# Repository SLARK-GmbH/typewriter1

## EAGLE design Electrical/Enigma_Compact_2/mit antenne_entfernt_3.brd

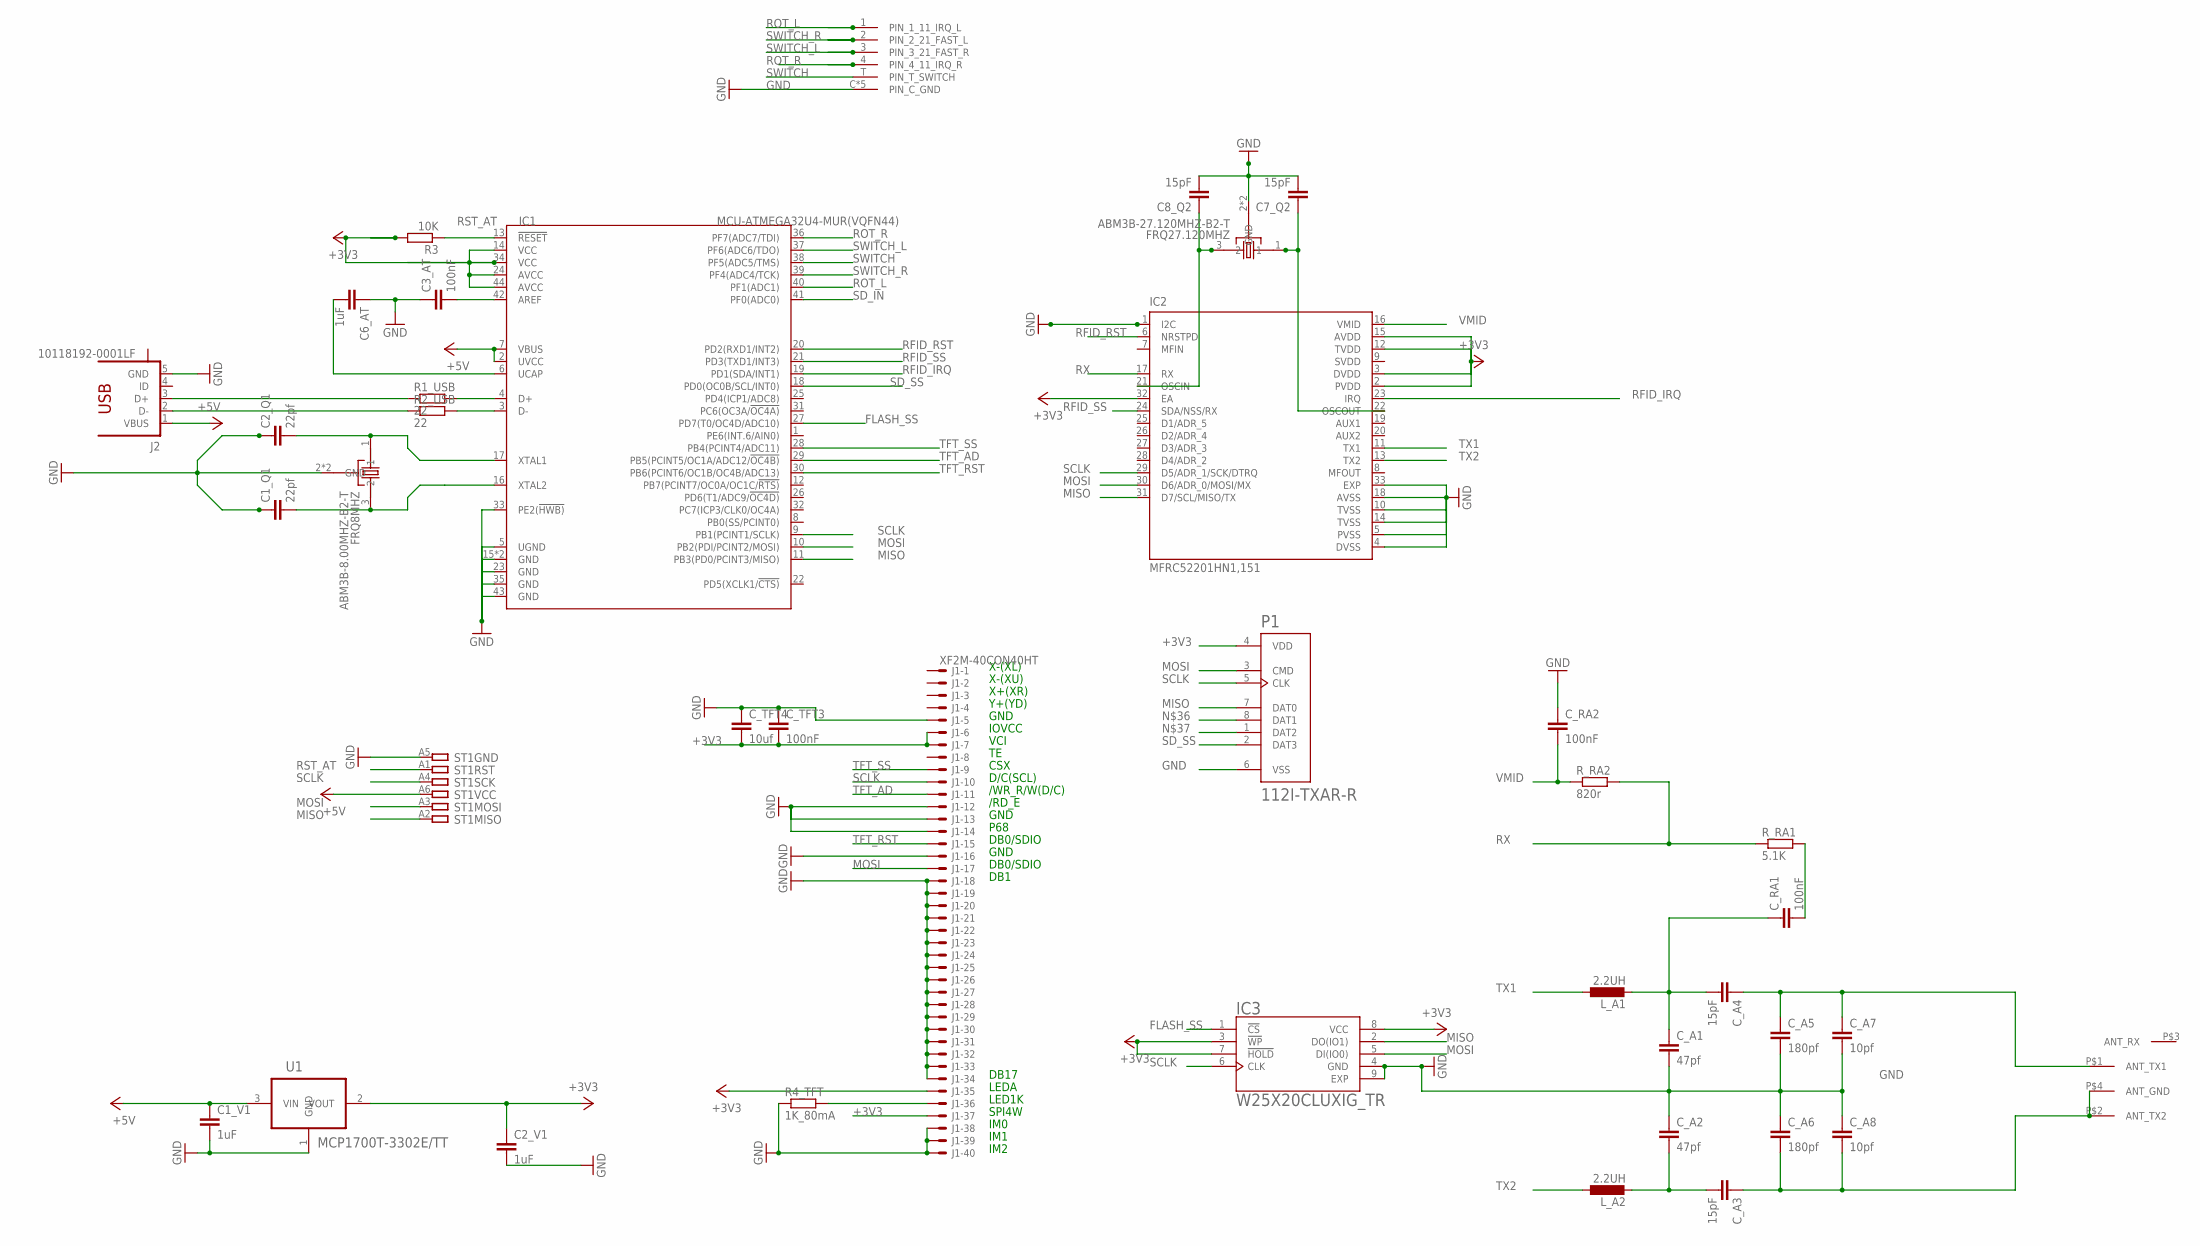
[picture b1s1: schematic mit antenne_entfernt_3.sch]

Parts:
C1_Q1, C2_Q1: 22pf; C0402K
C1_V1, C2_V1, C6_AT: 1uF; C0402K
C3_AT: 100nF; C0402K
C7_Q2, C8_Q2: 15pF; C0402K
C_A1, C_A2: 47pf; C0402K
C_A3: 15pF; C0402K
C_A4: 15pF; C0603K
C_A5, C_A6: 180pf; C0402K
C_A7, C_A8: 10pf; C0402K
C_RA1, C_RA2: 100nF; C0402K
C_TFT3: 100nF; C0402K
C_TFT4: 10uf; C0402K
FRQ8MHZ: ABM3B-8.00MHZ-B2-T; OSCSC500X320X110-4N
FRQ27.120MHZ: ABM3B-27.120MHZ-B2-T; OSCSC500X320X110-4N
IC1: MCU-ATMEGA32U4-MUR(VQFN44); QFN44G-0.5-7X7MM
IC2: MFRC52201HN1,151; QFN50P500X500X100-33N
IC3: W25X20CLUXIG_TR; SON50P300X200X60-9N
J1: XF2M-40CON40HT; XF2M-4015-1F
J2: 10118192-0001LF
L_A1, L_A2: 2.2UH; L2012C
P1: 112I-TXAR-R
R1_USB, R2_USB: 22; R0402
R3: 10K; R0402
R4_TFT: 1K_80mA; R0402
R_RA1: 5.1K; R0402
R_RA2: 820r; R0402
S1: WIPPSCHALTER_SCHWARZ_5WEGE; SMD_SWITCH1
S3: ANTENNE; ANTENNE_ENIGMA_34X44
ST1: ISA; IBM8BIT
U1: MCP1700T-3302E/TT; SOT95P237X112-3N

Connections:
+3V3: C2_V1.1, C_TFT3.2, C_TFT4.2, IC1.14 (VCC), IC1.24 (AVCC), IC1.34 (VCC), IC1.44 (AVCC), IC2.2 (PVDD), IC2.3 (DVDD), IC2.12 (TVDD), IC2.15 (AVDD), IC2.32 (EA), IC3.3 (!WP), IC3.7 (!HOLD), IC3.8 (VCC), J1.4 (MS), J1.6 (MS), J1.34 (MS), J1.35 (MS), P1.4 (VDD), R3.2, U1.2 (VOUT)
+5V: C1_V1.1, IC1.2 (UVCC), IC1.7 (VBUS), J2.1 (VBUS), ST1.A6, U1.3 (VIN)
FLASH_SS: IC1.27 (PD7(T0/OC4D/ADC10)), IC3.1 (!CS)
GND: C1_Q1.1, C1_V1.2, C2_Q1.1, C2_V1.2, C3_AT.1, C6_AT.1, C7_Q2.2, C8_Q2.2, C_A1.2, C_A2.1, C_A5.2, C_A6.1, C_A7.2, C_A8.1, C_RA2.1, C_TFT3.1, C_TFT4.1, FRQ8MHZ.2 (GND), FRQ8MHZ.4 (GND), FRQ27.120MHZ.2 (GND), FRQ27.120MHZ.4 (GND), IC1.5 (UGND), IC1.15 (GND), IC1.23 (GND), IC1.33 (PE2(!HWB)), IC1.35 (GND), IC1.43 (GND), IC1.TAB (GND), IC2.1 (I2C), IC2.4 (DVSS), IC2.5 (PVSS), IC2.10 (TVSS), IC2.14 (TVSS), IC2.18 (AVSS), IC2.33 (EXP), IC3.4 (GND), IC3.9 (EXP), J1.1 (MS), J1.2 (MS), J1.3 (MS), J1.7 (MS), J1.8 (MS), J1.9 (MS), J1.10 (MS), J1.11 (MS), J1.12 (MS), J1.13 (MS), J1.14 (MS), J1.15 (MS), J1.16 (MS), J1.17 (MS), J1.18 (MS), J1.19 (MS), J1.20 (MS), J1.21 (MS), J1.22 (MS), J1.23 (MS), J1.25 (MS), J1.27 (MS), J1.28 (MS), J1.29 (MS), J1.36 (MS), J1.M1 (MS), J1.M2 (MS), J2.5 (GND), P1.6 (VSS), R4_TFT.1, S1.C (PIN_C_GND), S1.C_1 (PIN_C_GND), S1.C_2 (PIN_C_GND), S1.C_3 (PIN_C_GND), S1.GND_TERMINAL (PIN_C_GND), ST1.A5, U1.1 (GND)
MISO: IC1.11 (PB3(PD0/PCINT3/MISO)), IC2.31 (D7/SCL/MISO/TX), IC3.2 (DO(IO1)), P1.7 (DAT0), ST1.A2
MOSI: IC1.10 (PB2(PDI/PCINT2/MOSI)), IC2.30 (D6/ADR_0/MOSI/MX), IC3.5 (DI(IO0)), J1.24 (MS), P1.3 (CMD), ST1.A3
unnamed: C1_Q1.2, FRQ8MHZ.3 (2), IC1.16 (XTAL2)
unnamed: C2_Q1.2, FRQ8MHZ.1, IC1.17 (XTAL1)
unnamed: C8_Q2.1, FRQ27.120MHZ.3 (2), IC2.21 (OSCIN)
unnamed: IC1.4 (D+), R1_USB.2
unnamed: IC1.3 (D-), R2_USB.2
unnamed: J2.3 (D+), R1_USB.1
unnamed: J2.2 (D-), R2_USB.1
unnamed: C7_Q2.1, FRQ27.120MHZ.1, IC2.22 (OSCOUT)
unnamed: C_A3.1, C_A6.2, C_A8.2, S3.P$2 (ANT_TX2), S3.P$4 (ANT_GND)
unnamed: C3_AT.2, IC1.42 (AREF)
unnamed: C6_AT.2, IC1.6 (UCAP)
unnamed: J1.5 (MS), R4_TFT.2
unnamed: C_RA1.2, R_RA1.2
unnamed: C_A2.2, C_A3.2, L_A2.2
unnamed: C_A1.1, C_A4.2, C_RA1.1, L_A1.2
unnamed: C_A4.1, C_A5.1, C_A7.1, S3.P$1 (ANT_TX1)
RFID_IRQ: IC1.19 (PD1(SDA/INT1)), IC2.23 (IRQ)
RFID_RST: IC1.20 (PD2(RXD1/INT2)), IC2.6 (NRSTPD)
RFID_SS: IC1.21 (PD3(TXD1/INT3)), IC2.24 (SDA/NSS/RX)
ROT_L: IC1.40 (PF1(ADC1)), S1.1 (PIN_1_11_IRQ_L)
ROT_R: IC1.36 (PF7(ADC7/TDI)), S1.4 (PIN_4_11_IRQ_R)
RST_AT: IC1.13 (!RESET), R3.1, ST1.A1
RX: IC2.17 (RX), R_RA1.1, R_RA2.2
SCLK: IC1.9 (PB1(PCINT1/SCLK)), IC2.29 (D5/ADR_1/SCK/DTRQ), IC3.6 (CLK), J1.31 (MS), P1.5 (CLK), ST1.A4
SD_IN: IC1.41 (PF0(ADC0))
SD_SS: IC1.18 (PD0(OC0B/SCL/INT0)), P1.2 (DAT3)
SVDD: IC2.9 (SVDD)
SWITCH: IC1.38 (PF5(ADC5/TMS)), S1.T (PIN_T_SWITCH)
SWITCH_L: IC1.37 (PF6(ADC6/TDO)), S1.3 (PIN_3_21_FAST_R)
SWITCH_R: IC1.39 (PF4(ADC4/TCK)), S1.2 (PIN_2_21_FAST_L)
TFT_AD: IC1.29 (PB5(PCINT5/OC1A/ADC12/!OC4B)), J1.30 (MS)
TFT_RST: IC1.30 (PB6(PCINT6/OC1B/OC4B/ADC13)), J1.26 (MS)
TFT_SS: IC1.28 (PB4(PCINT4/ADC11)), J1.32 (MS)
TX1: IC2.11 (TX1), L_A1.1
TX2: IC2.13 (TX2), L_A2.1
VMID: C_RA2.2, IC2.16 (VMID), R_RA2.1

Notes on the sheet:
X-(XL)
X-(XU)
X+(XR)
Y+(YD)
GND
IOVCC
VCI
CSX
D/C(SCL)
/WR_R/W(D/C)
/RD_E
P68
DB0/SDIO
DB1
DB17
LEDA
LED1K
SPI4W
IM1
IM0
IM2

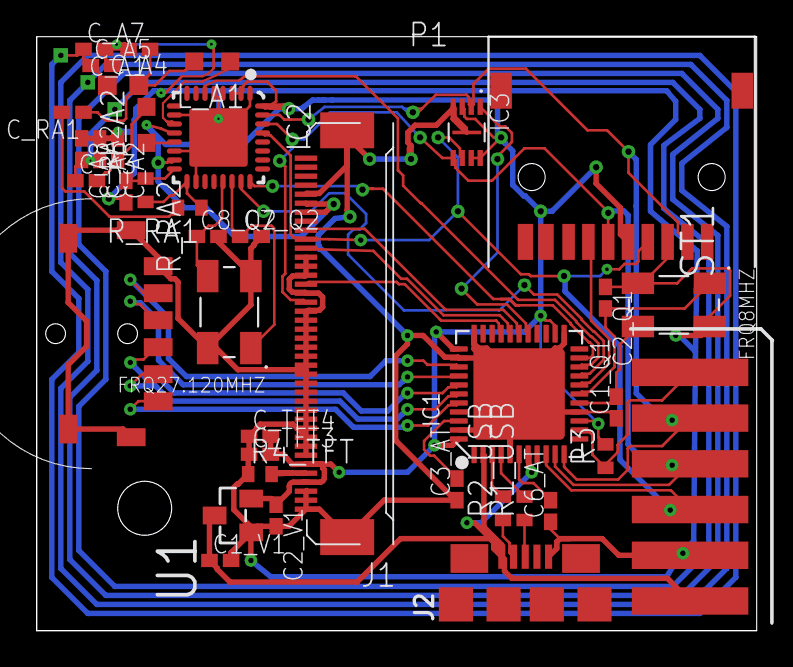
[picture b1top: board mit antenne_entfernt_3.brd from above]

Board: 2 copper layers, 40.0 x 33.0 mm, 40 parts (0 on the bottom side), 40 nets.

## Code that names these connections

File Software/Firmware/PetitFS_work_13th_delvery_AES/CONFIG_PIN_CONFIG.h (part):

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
//-----RFID----

#define RFID_RST 1
#define RFID_SS  0
#define RFID_IRQ 2

//-----Crypt

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
//-----SD-Karte----

#define SD_SS 3

//-----SPI-Flash----

#define FLASH_SS 6

//-----Display----

#define TFT_SS   8
#define TFT_AD   9
#define TFT_RST 10

//-----Taster----

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
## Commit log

2020-11-16 Initial project collection upload
